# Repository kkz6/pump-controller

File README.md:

# Pump starter controller

Current main-board revision: **DIRECT-R4-PROTOTYPE**. [PCB manufacturing review](verification/dfm-review-2026-11-24/R4/README.md) · [Matching JLC upload bundle](manufacturing/pump-controller-R4-JLC-upload.zip). Supplier placement approval and physical bring-up remain pending.

For the current JLC replacement, use the [local-relay assembly variant](manufacturing/pump-controller-R4-local-relays-JLC-upload.zip): K1/K2 are fitted locally, while J30/J35 remain factory-assembled. The full R4 bundle above remains available for assembling the relays at JLC.

A two-board prototype for an existing 1.5 HP, 220 V single-phase pump starter. The main board measures supply voltage, reads a current transformer and tank probes, and issues starter commands through two PCB-mounted high-inrush changeover relays. The door panel has a plug-in OLED, five operator buttons, an optional key selector and an external button connector. The existing starter switches the motor and capacitors.

| What you need | Files |
| --- | --- |
| Edit the main circuit or board | [Main KiCad project](hardware/main/pump-direct.kicad_pro) · [Schematic PDF](docs/main-schematic.pdf) · [Board drawing](docs/main-board.svg) |
| Edit the door panel | [Panel KiCad project](hardware/panel/pump-panel-rev-f.kicad_pro) · [Schematic PDF](docs/panel-schematic.pdf) · [Panel with display, STEP](mechanical/panel/pump-panel-rev-f-with-display.step) |
| Identify a terminal or relay | [Starter interfaces and connectors](docs/connections.md) |
| Program or recover the processor | [USB bench guide](docs/programming.md) · [Bench firmware](firmware/bench) |
| Request bare boards and assembly | [Manufacturing package and cost](manufacturing/README.md) |
| Order parts and boards | [Order checklist](manufacturing/order-checklist.md) |
| Bring up a new board | [First power-up checks](docs/bring-up.md) |
| Reproduce the design checks | [Verification](verification/README.md) · [Design review 2026-11-21](verification/design-review-2026-11-21.md) |
| See the boards in 3D | [3D views](docs/3d/README.md) · [Main board STL](docs/3d/main.stl) · [Panel STL](docs/3d/panel.stl) |

## Hardware

The main PCB is 100 × 118.5 mm with six copper layers. Relay outputs face outward at the bottom; tank/inlet ports face outward at the top. Printed guides identify K1 with J30 (A) and K2 with J35 (B). R4 uses Omron G5RL-1-E-HR DC5 relays and three-way screw terminals: 1 NO, 2 COM, 3 NC. The full factory-assembly BOM includes the relays and output terminals; the current order uses the local-relay variant linked above. The two outputs can serve a conventional self-holding DOL or a starter with documented remote inputs. Select the control profile for the specific starter. The 60 × 45 mm two-layer panel connects to main J32 through a keyed 12-way cable.

The main board uses an ESP32-C6-MINI-1U-H4 (4 MB flash). The two dedicated programming buttons and USB application indicators are on its low-voltage side. Operator START, STOP, MODE, SET and NEXT are on the panel. The repository includes a flashable USB bench image, control components and tests. Operational wireless firmware, pairing with a particular hub, enclosure fit and physical starter qualification remain open.

The design is at prototype stage. The original DOL STOP and overload must independently interrupt the contactor coil. A welded pickup contact can restart some starters when STOP is released. Review that behavior and the actual coil specification before commissioning. [Interface details](docs/connections.md)

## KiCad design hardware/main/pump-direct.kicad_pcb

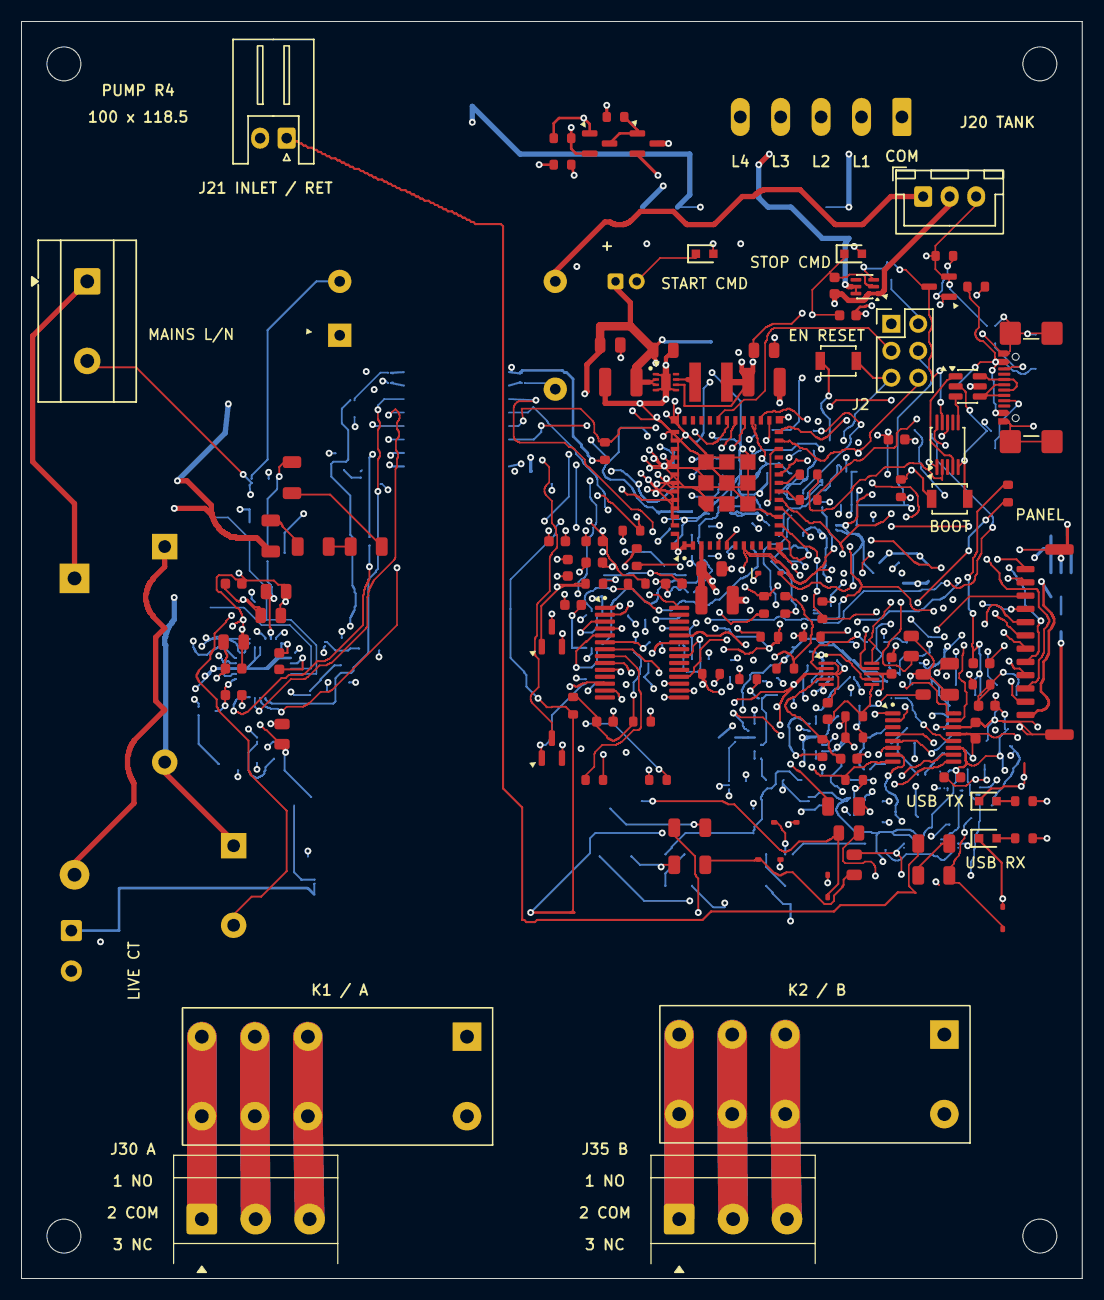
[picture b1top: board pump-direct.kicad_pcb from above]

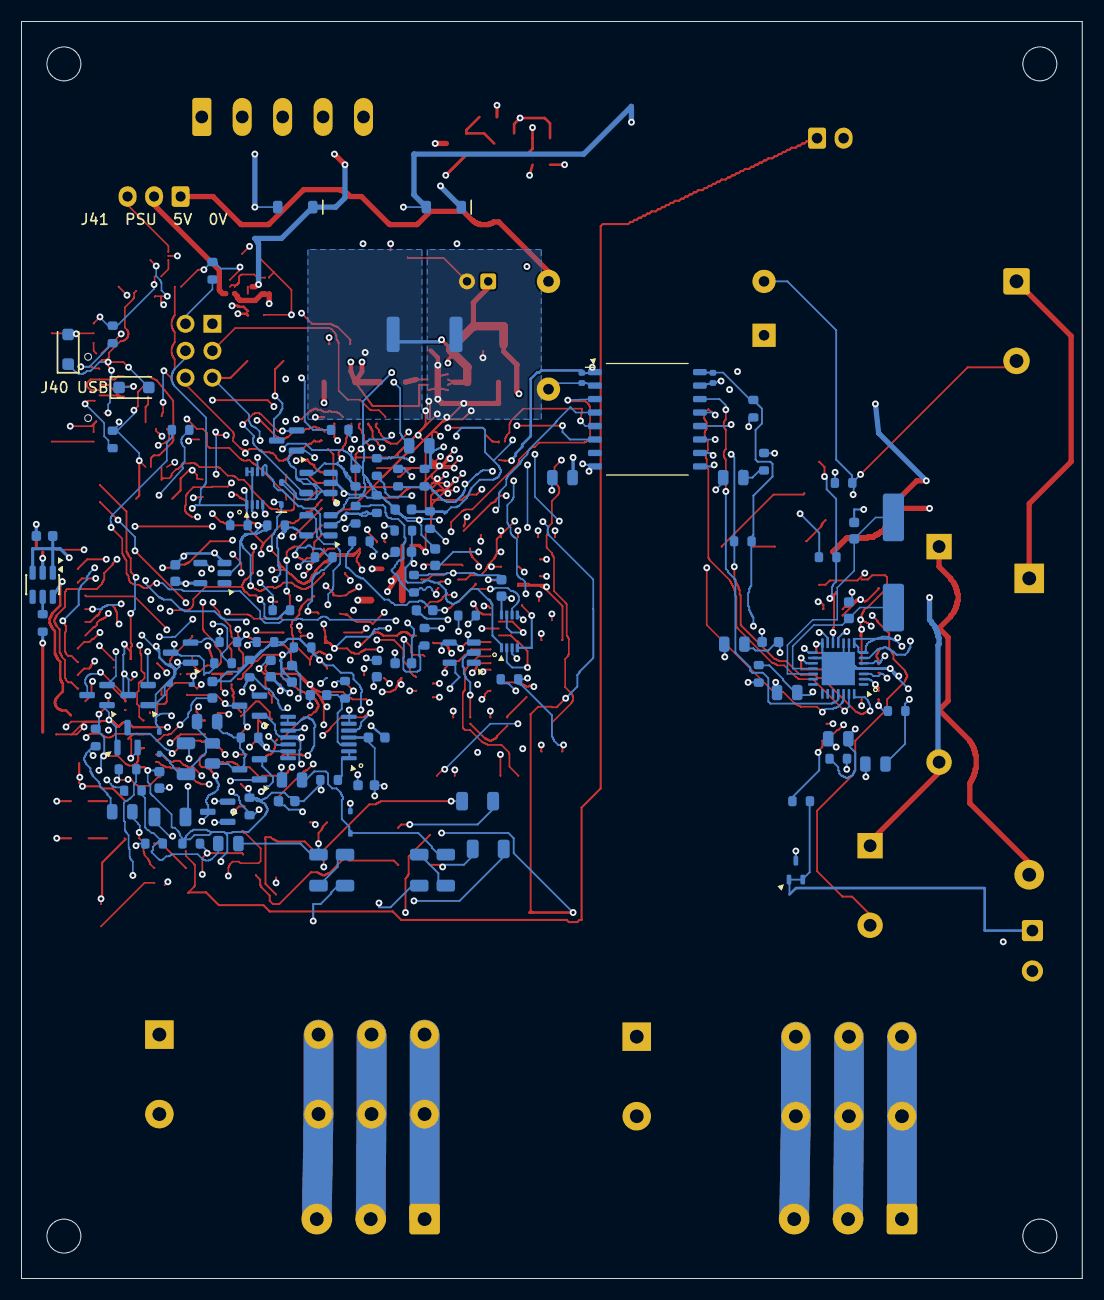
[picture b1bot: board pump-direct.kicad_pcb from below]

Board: 6 copper layers, 100.0 x 118.5 mm, 242 parts (117 on the bottom side), 154 nets.

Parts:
C1: 47uF 25V 105C; CP_Radial_D5_P2_Pads1p5
C2, C4, C6, C21: 1uF 50V X7R; C_0805_2012Metric
C3, C5: 22uF 16V X7R; C_1210_3225Metric
C20: 22uF 10V X7R; C_1210_3225Metric
C22: 1uF 10V X7R; C_0805_2012Metric
C40, C42, C44: 4.7uF; C_0805_2012Metric
C41, C43, C45, C47, C70, C71, C72, C73, C75, C76, C77, C78, C88, C90, C100, C102, C103, C104: 100nF; C_0603_1608Metric
C46, C55, C58: 22uF; C_0805_2012Metric
C48, C74, C101, C105: 1uF; C_0603_1608Metric
C49, C50: 33pF; C_0603_1608Metric
C51, C52, C53, C54: 33nF 50V X7R 10%; C_0805_2012Metric
C57, C60: 100nF; C_0402_1005Metric
C80, C82, C84, C86, C110, C111, C112, C113: 10nF; C_0603_1608Metric
C106, C107, C108, C109, C120, C122, C124, C126, C128: 1uF; C_0805_2012Metric
C121, C123, C125, C127, C129: 1nF; C_0603_1608Metric
C240: 1uF 50V X5R; C_0603_1608Metric
C241, C242, C243: 100nF 16V X7R; C_0603_1608Metric
D10: BAV99W; SOT-323_SC-70
D30, D35: BAT54WS; D_SOD-323
D31, D32: 1N4148W; D_SOD-123
D40: START CMD GREEN; Kingbright_1608_LowCurrent
D41: STOP CMD RED; Kingbright_1608_LowCurrent
D42: USB ESD; SOT-23-6
D43: CLAMP REFERENCE BLOCK; D_SOD-123F
D44: VBUS TVS 6V; D_SOD-123F
D60: USB TX; Kingbright_1608_LowCurrent
D61: USB RX; Kingbright_1608_LowCurrent
D100, D101, D110, D112, D114, D116, D118: PESD5V0S1BA; D_SOD-323
D102, D103, D111, D113, D115, D117, D119: BAS70-04; SOT-23
F1: T1A 600VAC; Fuse_Axial_5x20_P27.94
FB1, FB2: 0R; R_0603_1608Metric
H1, H2, H3, H4: M3 nylon mount; MountingHole_3.2mm_M3
J1: AC INPUT L/N; TerminalBlock_MetzConnect_Type171_RT13702HBWC_1x02_P7.50mm_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
J2: SERVICE 2x3; PinHeader_2x03_P2.54mm_Vertical
J10: LIVE CT / FIXED; TerminalBlock_Phoenix_MKDS-1-2-3.81_1x02_P3.81mm_Horizontal
J20: TANK PROBES; PhoenixContact_MC_1,5_5-G-3.81_1x05_P3.81mm_Horizontal
J21: INLET / RETURN; JST_XH_S2B-XH-A_1x02_P2.50mm_Horizontal
J30: OUT A / NO-COM-NC; MKDS3_3_508_Power
J32: PANEL / GH12; JST_GH_SM12B-GHS-TB_1x12-1MP_P1.25mm_Horizontal
J35: OUT B / NO-COM-NC; MKDS3_3_508_Power
J40: USB-C DATA / SERVICE; USB_C_GCT_USB4110_12Lands
J41: RUN LINK / BENCH 5V; JST_XH_B3B-XH-A_1x03_P2.50mm_Vertical
K1, K2: G5RL-1-E-HR DC5; G5RL_1_E_HR
L1: 2.2uH; L_Sunlord_SWPA4030S
Q30, Q31: AO3400A; SOT-23
Q40: VBUS INHIBIT; SOT-23
Q50: STOP COIL HIGH SIDE; SOT-23
Q51: STOP PERMIT INVERTER; SOT-23
R1: 22R 3W FUSIBLE; R_Axial_L13_D6_P20.32
R2: 33R 1% 2W MINIMUM LOAD; R_2512_6332Metric_DNP_NoPaste
R20, R21, R22, R26, R40, R41, R80, R82, R84, R89, R91, R100, R101, R109: 10k; R_0603_1608Metric
R24, R25, R71, R72, R77, R78, R115, R118: 2.2k; R_0603_1608Metric
R27, R28, R76: 22R; R_0603_1608Metric
R42: 0R; R_0603_1608Metric
R43, R44, R45, R46: 249k; R_1206_3216Metric
R47, R48, R49, R50, R88, R90, R110, R112, R190, R191, R260, R261: 1k; R_0603_1608Metric
R70, R132, R142, R152, R162, R172: 47k; R_0603_1608Metric
R74: 100R; R_0603_1608Metric
R75, R87, R92, R93, R105, R106, R107, R108: 100k; R_0603_1608Metric
R81, R83, R85, R104: 33k; R_0603_1608Metric
R86, R103, R133, R143, R153, R163, R173: 22k; R_0603_1608Metric
R102, R111, R113: 100; R_0603_1608Metric
R114: 1M; R_0603_1608Metric
R116, R117, R119, R120, R130, R131, R140, R141, R150, R151, R160, R161, R170, R171: 10k; R_1206_3216Metric
R240, R241: 5.1k 1%; R_0603_1608Metric
R242: 1k 1%; R_0603_1608Metric
R243: 47k 1%; R_0603_1608Metric
R244, R247: 10k 1%; R_0603_1608Metric
R245: 210k 1%; R_0603_1608Metric
R246, R248: 100k 1%; R_0603_1608Metric
RV1: TMOV 320VAC; TMOV14_Inline_P7.5
SW60: BOOT; SW_SPST_B3U-1000P
SW61: EN RESET; SW_SPST_B3U-1000P
U1: 5V 1.2A ISOLATED; RACM06E
U2: TPS62162 3V3 1A; Texas_DSG0008A_WSON-8-1EP_2x2mm_P0.5mm_EP0.9x1.6mm
U3: ESP32-C6-MINI-1U-H4; ESP32-C6-MINI-1U
U10: ADE7953ACPZ; LFCSP-28-1EP_5x5mm_P0.5mm_EP3.14x3.14mm
U11: CA-IS3641HW; CA-IS3641_SOIC16W_Dense
U20: TLV9004; TSSOP-14_4.4x5mm_P0.65mm
U21: TMUX1208; TSSOP-16_4.4x5mm_P0.65mm
U22: ADS1115; TSSOP-10_3x3mm_P0.5mm
U30: STWD100NYWY3F / 1.6s; SOT-23-5
U31: SN74LVC1G74DCUR; SN74LVC1G74_DCU_TI
U32: MCP120T-300I/TT; SOT-23
U33: MCP23017-E/SS; SSOP-28_5.3x10.2mm_P0.65mm
U34: 74LVC1G08GV; SOT-23-5
U35, U36: SN74LVC1G17DBVR; SOT-23-5
U37: 74LVC3G17DC; SN74LVC3G17_DCU_TI
U40: USB MOTOR INHIBIT; SOT-363_SC-70-6
U41: USB DATA SWITCH; MSOP-10_3x3mm_P0.5mm
U42: PANEL 5V LIMIT; SOT-23-6
Y1: 3.579545MHz / CL20pF; Crystal_SMD_HC49-SD

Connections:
+3V3: C5.1, C6.1, C20.1, C21.1, C57.1, C70.1, C71.1, C72.1, C73.1, C74.1, C75.1, C76.1, C77.1, C78.1, C102.1, C103.1, C104.1, C105.1, C241.1, D102.2, D103.2, D111.2, D113.2, D115.2, D117.2, D119.2, J2.2 (3V3_SENSE), J32.8 (+3V3), L1.2, R20.1, R21.1, R22.1, R24.1, R25.1, R26.1, R70.1, R89.1, R91.1, R100.1, R109.2, R244.1, U2.6, U3.3, U11.1, U20.4, U21.2, U21.13, U22.8, U30.5, U31.2, U31.7, U31.8, U32.2, U33.9 (VDD), U34.5, U35.5, U36.5, U37.8, U41.10 (VCC)
+5V: C1.1, C2.1, C3.1, C4.1, C55.1, C240.1, J41.2 (BOARD_5V), R2.1, U2.2, U2.3, U40.1 (VIN)
+5V_CMD: C242.1, C243.1, D32.1 (K), K2.8, Q50.2, R246.1, U40.5 (QOD), U40.6 (VOUT), U42.1, U42.3
ARM_CLEAR_N: U31.6, U36.4
ARM_CMD: J2.4 (ARM_TEST), R78.1, U3.30, U31.1
ARM_Q: U31.5, U34.1
AUTO_RETURN: J32.4 (AUTO_RETURN), R84.1
AUTO_SENSE: U33.5 (GPB4), U37.2
AUTO_SENSE_RAW: C84.1, R84.2, R85.1, U37.6
BOOT: J2.6 (BOOT_N), R21.2, SW60.1, U3.23
BUCK_SW: L1.1, U2.7
CMD_ALLOWED: Q40.3, R244.2, U40.3 (ON), U41.9 (OE_N)
CTRL_A_COM: J30.2, K1.3, K1.6
CTRL_A_NC: J30.3, K1.2, K1.7
CTRL_A_NO: J30.1, K1.4, K1.5
CTRL_B_COM: J35.2, K2.3, K2.6
CTRL_B_NC: J35.3, K2.2, K2.7
CTRL_B_NO: J35.1, K2.4, K2.5
GND: C1.2, C2.2, C3.2, C4.2, C5.2, C6.2, C20.2, C21.2, C22.2, C55.2, C57.2, C70.2, C71.2, C72.2, C73.2, C74.2, C75.2, C76.2, C77.2, C78.2, C80.2, C82.2, C84.2, C86.2, C88.2, C90.2, C100.2, C101.2, C102.2, C103.2, C104.2, C105.2, C110.2, C111.2, C112.2, C113.2, C240.2, C241.2, C242.2, C243.2, D40.1 (K), D41.1 (K), D42.2 (GND), D44.2 (A), D60.1 (K), D61.1 (K), D100.2, D101.2, D102.1, D103.1, D110.2, D111.1, D112.2, D113.1, D114.2, D115.1, D116.2, D117.1, D118.2, D119.1, J2.1 (GND), J32.7 (GND), J32.MP (MOUNT), J40.A1 (GND_A1_B12), J40.A12 (GND_A12_B1), J40.SH (SHIELD), J41.3 (RETURN), Q30.2, Q31.2, Q40.2, Q51.2, R2.2, R71.2, R72.2, R75.2, R77.2, R78.2, R81.2, R83.2, R85.2, R87.2, R92.2, R93.2, R101.2, R105.2, R106.2, R107.2, R108.2, R240.2, R241.2, R243.2, R245.2, R248.2, SW60.2, SW61.2, U1.4 (-VOUT), U2.1, U2.4, U2.5, U2.9, U3.1, U3.2, U3.11, U3.14, U3.36, U3.37, U3.38, U3.39, U3.40, U3.41, U3.42, U3.43, U3.44, U3.45, U3.46, U3.47, U3.48, U3.49, U3.50, U3.51, U3.52, U3.53, U11.2, U11.8, U20.11, U21.14, U22.1, U22.3, U30.2, U30.3, U31.4, U32.3, U33.10 (VSS), U33.15 (A0), U33.16 (A1), U33.17 (A2), U34.3, U35.3, U36.3, U37.4, U40.2 (GND), U41.1 (SEL), U41.5 (GND), U42.2
HEARTBEAT: R71.1, U3.27, U30.4
HH_SENSE: C86.1, R86.2, R87.1, U35.2
I2C_SCL: J32.10 (I2C_SCL), R25.2, U3.29, U22.10, U33.12 (SCL)
I2C_SDA: J32.9 (I2C_SDA), R24.2, U3.28, U22.9, U33.13 (SDA)
INTERLOCK_OK: D35.1, U33.6 (GPB5), U35.4
K1_5V: D31.1 (K), K1.8, Q50.3
K1_GATE: Q30.1, R74.2, R75.1
K1_LOW: D31.2 (A), K1.1, Q30.3
K1_PBASE: Q51.1, R247.2, R248.1
K1_PGATE: Q50.1, Q51.3, R246.2
K2_GATE: Q31.1, R76.2, R77.1
K2_LOW: D32.2 (A), K2.1, Q31.3
L_FUSED: F1.2, R1.1
L_PROTECTED: R1.2, R43.1, RV1.1, U1.1 (AC_L)
MAINS_L: F1.1, J1.1 (L)
MAINS_N: J1.2 (N), R42.1, RV1.2, U1.2 (AC_N)
MAN_RETURN: J32.3 (MAN_RETURN), R82.1
MAN_SENSE: U33.4 (GPB3), U37.5
MAN_SENSE_RAW: C82.1, R82.2, R83.1, U37.3
MCU_EN: C22.1, D30.1, J2.5 (RESET_N), R20.2, SW61.1, U3.8, U33.18 (RESET_N)
METER_CS: R26.2, U3.24, U11.5
METER_MISO: U3.19, U11.6
METER_MOSI: U3.16, U11.4
METER_SCLK: U3.15, U11.3
MUX_A0: R106.1, U3.13, U21.1
MUX_A1: R107.1, U3.5, U21.16
MUX_A2: R108.1, U3.6, U21.15
M_3V3: C46.1, C47.1, C60.1, FB1.2, R40.1, R41.1, U10.7, U10.8, U10.17, U11.16
M_CS: R41.2, U10.28, U11.12
M_CT_HI: D10.1, D10.2, J10.1, R49.1
M_GND: C40.2, C41.2, C42.2, C43.2, C44.2, C45.2, C46.2, C47.2, C48.2, C49.2, C50.2, C51.2, C52.2, C53.2, C54.2, C60.2, D10.3, FB2.2, J10.2, R42.2, R47.2, R48.1, R50.1, U10.4, U10.9, U10.10, U10.14, U10.16, U10.29, U11.9, U11.10, U11.15
M_IAN: C54.1, R50.2, U10.6
M_IAP: C53.1, R49.2, U10.5
M_ISO_GND: C58.2, FB2.1
M_ISO_RAW: C58.1, FB1.1
M_MISO: U10.26, U11.11
M_MOSI: U10.27, U11.13
M_REF: C44.1, C45.1, U10.13
M_RESET_N: C48.1, R40.2, U10.2
M_SCLK: U10.25, U11.14
M_VDIV_0: R43.2, R44.1
M_VDIV_1: R44.2, R45.1
M_VDIV_2: R45.2, R46.1
M_VINTA: C42.1, C43.1, U10.15
M_VINTD: C40.1, C41.1, U10.3
M_VN: C52.1, R48.2, U10.11
M_VP: C51.1, R46.2, R47.1, U10.12
M_XIN: C49.1, U10.18, Y1.1
M_XOUT: C50.1, U10.19, Y1.2
PANEL_5V: J32.1 (+5V), U42.6
PANEL_ILIM: R245.1, U42.5
PERMIT_D: R72.1, U3.26, U34.2
PERMIT_Q: R74.1, U34.4
PROBE_ADC_BIAS: C111.1, R111.2, U22.5
PROBE_ADC_BIAS2: C113.1, R113.2, U22.7
PROBE_ADC_RDY: R109.1, U22.2
PROBE_ADC_SIGNAL: C110.1, R110.2, U22.4
PROBE_ADC_TX: C112.1, R112.2, U22.6
PROBE_BIAS: C101.1, C121.2, C123.2, C125.2, C127.2, C129.2, R102.2, R104.1, R111.1, R113.1, R114.2, R132.2, R142.2, R152.2, R162.2, R172.2, U21.11
PROBE_BIAS_DIV: C100.1, R100.2, R101.1, U20.3
PROBE_BIAS_RAW: R102.1, U20.1, U20.2
PROBE_EXC: R103.1, R105.1, U3.12
PROBE_ICOM: J21.2, R120.2
PROBE_ICOM_CLAMP: C107.2, C109.2, D101.1, R119.1
PROBE_ICOM_DRIVE: C107.1, C109.1, D103.3, R118.2
PROBE_ICOM_MID: R119.2, R120.1
PROBE_INLET: J21.1, R170.1
PROBE_INLET_ADC: C129.1, D119.3, R173.2, U21.12
PROBE_INLET_CLAMP: C128.1, D118.1, R171.2
PROBE_INLET_MID: R170.2, R171.1
PROBE_INLET_SENSE: C128.2, R172.1, R173.1
PROBE_L1: J20.2, R130.1
PROBE_L1_ADC: C121.1, D111.3, R133.2, U21.4
PROBE_L1_CLAMP: C120.1, D110.1, R131.2
PROBE_L1_MID: R130.2, R131.1
PROBE_L1_SENSE: C120.2, R132.1, R133.1
PROBE_L2: J20.3, R140.1
PROBE_L2_ADC: C123.1, D113.3, R143.2, U21.5
PROBE_L2_CLAMP: C122.1, D112.1, R141.2
PROBE_L2_MID: R140.2, R141.1
PROBE_L2_SENSE: C122.2, R142.1, R143.1
PROBE_L3: J20.4, R150.1
PROBE_L3_ADC: C125.1, D115.3, R153.2, U21.6
PROBE_L3_CLAMP: C124.1, D114.1, R151.2
PROBE_L3_MID: R150.2, R151.1
PROBE_L3_SENSE: C124.2, R152.1, R153.1
PROBE_L4: J20.5, R160.1
PROBE_L4_ADC: C127.1, D117.3, R163.2, U21.7
PROBE_L4_CLAMP: C126.1, D116.1, R161.2
PROBE_L4_MID: R160.2, R161.1
PROBE_L4_SENSE: C126.2, R162.1, R163.1
PROBE_MUX_BUF: R110.1, U20.8, U20.9
PROBE_MUX_OUT: R114.1, U20.10, U21.8
PROBE_TCOM: J20.1, R117.2
PROBE_TCOM_CLAMP: C106.2, C108.2, D100.1, R116.1
PROBE_TCOM_DRIVE: C106.1, C108.1, D102.3, R115.2
PROBE_TCOM_MID: R116.2, R117.1
PROBE_TX_INLET: R118.1, U20.13, U20.14, U21.9
PROBE_TX_SET: R103.2, R104.2, U20.5, U20.12
PROBE_TX_TANK: R112.1, R115.1, U20.6, U20.7, U21.10
PSU_5V_RAW: J41.1 (PSU), U1.5 (+VOUT)
RESET_FILTER: C90.1, R90.2, R91.2, U33.2 (GPB1)
RESET_N: J32.6 (RESET_N), R90.1
RUN_CMD: R76.1, U3.25
SAFE_CLEAR_N: D30.2, D35.2, R70.2, U30.1, U32.1, U36.2
SPARE_B6: J32.11 (SPARE_B6), R92.1, U33.7 (GPB6)
SPARE_B7: J32.12 (SPARE_B7), R93.1, U33.21 (GPA0)
START_CMD_LED: R190.1, U33.8 (GPB7)
START_FILTER: C88.1, R88.2, R89.2, U33.1 (GPB0)
START_LED_A: D40.2 (A), R190.2
START_N: J32.5 (START_N), R88.1
STOP_CMD_LED: R191.1, U33.28 (GPA7)
STOP_LED_A: D41.2 (A), R191.2
STOP_RETURN: J32.2 (STOP_RETURN), R80.1, R86.1, R247.1
STOP_SENSE: U33.3 (GPB2), U37.7
STOP_SENSE_RAW: C80.1, R80.2, R81.1, U37.1
STRAP_GPIO8: R22.2, U3.22
UART_TX: J2.3 (TXD0), U3.31
USB_CC1: J40.A5 (CC1), R240.1
USB_CC2: J40.B5 (CC2), R241.1
USB_CONN_DM: D42.4 (IO2), J40.A7 (D-), J40.B7 (D-)
USB_CONN_DP: D42.6 (IO1), J40.A6 (D+), J40.B6 (D+)
USB_DM: R27.2, U41.8 (D1-)
USB_DM_MCU: R27.1, U3.17
USB_DP: R28.2, U41.2 (D1+)
USB_DP_MCU: R28.1, U3.18
USB_ESD_REF: D42.5 (VBUS), D43.1 (K)
USB_PRESENT: Q40.1, R242.2, R243.1
USB_PROT_DM: D42.3 (IO2), U41.6 (D-)
USB_PROT_DP: D42.1 (IO1), U41.4 (D+)
USB_RX_IND: R261.1, U33.24
USB_RX_LED_A: D61.2 (A), R261.2
USB_TX_IND: R260.1, U33.23 (GPA2)
USB_TX_LED_A: D60.2 (A), R260.2
USB_VBUS: D43.2 (A), D44.1 (K), J40.A4 (VBUS_A4_B9), J40.A9 (VBUS_A9_B4), R242.1

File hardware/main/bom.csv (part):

Reference,Value,MPN,Description,Footprint,Datasheet,Sheet,DNP
J1,AC INPUT L/N,KF128-7.5-2P,"Cixi Kefa KF128-7.5, 2 positions on 7.50 mm pitch, rising-clamp screw terminal; UL 300 V 10 A, IEC 450 V 24 A OVC III. Pin 1 line, pin 2 neutral. Body is 0.5 mm wider than the Metz Type 171 courtyard; the footprint's 1.3 mm holes take its 0.8 mm pins.",CompactGuard:TerminalBlock_MetzConnect_Type171_RT13702HBWC_1x02_P7.50mm_Horizontal,https://jlcpcb.com/parts/componentSearch?searchTxt=C474954,power,False
F1,T1A 600VAC,0ADKP1000-RE,Bel 1 A time-delay axial pigtail fuse; 200 A interrupting capacity at 600 VAC; coordinate with upstream protection,Pump:Fuse_Axial_5x20_P27.94,https://www.belfuse.com/media/datasheets/products/circuit-pr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,power,False
R1,22R 3W FUSIBLE,AC03000002209JACCS,Vishay AC03-CS 22 ohm 3 W 5% fusible safety resistor; keep heat away from MCU and capacitors,Pump:R_Axial_L13_D6_P20.32,https://www.vishay.com/docs/28909/acxxcs.pdf,power,False
RV1,TMOV 320VAC,TMOV14RP320EL2T7,"Thermally protected 14 mm MOV, 320 VAC continuous; INLINE crimped L2 lead option (L2T7 tape or L2B7 bulk) required for footprint; surge coordination unverified",Pump:TMOV14_Inline_P7.5,https://www.littelfuse.com/assetdocs/tmov-itmov?assetguid=bd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,power,False
U1,5V 1.2A ISOLATED,RACM06E-05SK/277,"6 W reinforced-isolation AC/DC module, 25.4 x 25.4 x 16.7 mm; 5 V model delivers 6 W to 50 C at 115-277 VAC; keep output floating",Pump:RACM06E,https://recom-power.com/pdf/Powerline_AC-DC/RACM06E-K_277.pdf,power,False
C1,47uF 25V 105C,NXB25V47M5*11 LO,"SamYoung NXB, 47 uF, 25 V, 105 C, D5 x 11 mm. Front mounted on 2 mm lead pitch. Allow a 5.5 mm maximum diameter and 12.5 mm maximum length, up to 1 mm seating gap and up to 3 mm lead projection on the rear.",PumpRevE:CP_Radial_D5_P2_Pads1p5,https://jlcpcb.com/partdetail/SamYoungElectronics-NXB25V47M5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,power,False
C2,1uF 50V X7R,Generic 1uF 50V X7R 0805,Local ceramic bypass; X7R dielectric; verify effective capacitance at bias,Capacitor_SMD:C_0805_2012Metric,,power,False
C3,22uF 16V X7R,CL32B226KOJNNNE,"Samsung CL32B 1210, 22 uF, 16 V X7R, 10%. Buck VIN bypass. Verify at least 10 uF effective at operating bias and temperature.",Capacitor_SMD:C_1210_3225Metric,https://jlcpcb.com/partdetail/56557-CL32B226KOJNNNE/C55530,power,False
C4,1uF 50V X7R,Generic 1uF 50V X7R 0805,Buck high-frequency input bypass directly at VIN/PGND,Capacitor_SMD:C_0805_2012Metric,,power,False
U2,TPS62162 3V3 1A,TPS62162DSGR,"Fixed3.3V buck; FB to AGND, VOS Kelvin to output capacitor. Solder EP to GND; two external0.65/0.30mm GND vias, no holes in SMT land.",Package_SON:Texas_DSG0008A_WSON-8-1EP_2x2mm_P0.5mm_EP0.9x1.6mm,https://www.ti.com/lit/ds/symlink/tps62160.pdf,power,False
L1,2.2uH,SWPA4030S2R2MT,"Sunlord SWPA4030S, 4.0x4.0x3.0 mm; manufacturer land pattern: two 1.10x3.70 mm pads at +/-1.50 mm, 1.90 mm gap. Non-polarized. 2.2 uH 20%, 4.9 A saturation, 39 mOhm max DCR.",Inductor_SMD:L_Sunlord_SWPA4030S,https://jlcpcb.com/partdetail/Sunlord-SWPA4030S2R2MT/C36409,power,False
C5,22uF 16V X7R,CL32B226KOJNNNE,"Samsung CL32B 1210, 22 uF, 16 V X7R, 10%. Buck output bypass at the VOS sense point. Verify filter stability and rail load steps.",Capacitor_SMD:C_1210_3225Metric,https://jlcpcb.com/partdetail/56557-CL32B226KOJNNNE/C55530,power,False
C6,1uF 50V X7R,Generic 1uF 50V X7R 0805,Local 3.3 V rail bypass,Capacitor_SMD:C_0805_2012Metric,,power,False
R2,33R 1% 2W MINIMUM LOAD,CRM2512-FX-33R0ELF,"DNP: RECOM RACM06E minimum load is 0%, so no preload is fitted; footprint kept. Was Bourns 2512 thick-film 33 ohm 1%, 2 W at 70 C with 300 mm2 combined solder-pad/trace copper per datasheet; permanent 5 V minimum-load resistor, 0.677-0.844 W at 4.75-5.25 V including 1% tolerance. Reserve copper area and keep away from probes, precision meter components, antenna module and electrolytics. Revised module local ambient limit 50 C.",PumpRevE:R_2512_6332Metric_DNP_NoPaste,https://www.bourns.com/docs/product-datasheets/crm.pdf,power,True
U3,ESP32-C6-MINI-1U-H4,ESP32-C6-MINI-1U-H4,4 MB flash (H8 out of stock at JLC; same module and footprint); external antenna; hardware supports Matter over Wi-Fi or Thread. Antenna must be outside metal starter enclosure. GPIO17 drives ARM_CMD interlock rearm; GPIO16 UART TX logs only; GPIO4/5/15 unused; strap levels preserved.,Pump:ESP32-C6-MINI-1U,https://documentation.espressif.com/esp32-c6-mini-1_mini-1u_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,mcu,False
C20,22uF 10V X7R,Generic 22uF 10V X7R 1210,Module bulk capacitor adjacent to pin 3; effective capacitance >=10 uF at 3.3 V,Capacitor_SMD:C_1210_3225Metric,,mcu,False
C21,1uF 50V X7R,Generic 1uF 50V X7R 0805,Module bypass immediately at pin 3 and ground pads,Capacitor_SMD:C_0805_2012Metric,,mcu,False
C22,1uF 10V X7R,Generic 1uF 10V X7R 0805,Enable RC delay with R20; watchdog/supervisor uses open-drain reset only,Capacitor_SMD:C_0805_2012Metric,,mcu,False
R20,10k,"SPEC: 10k 1%, 0.1W, 0603",Module EN pull-up; 10 ms nominal RC with C22,Resistor_SMD:R_0603_1608Metric,,mcu,False
R21,10k,"SPEC: 10k 1%, 0.1W, 0603",GPIO9 boot strap pull-up. An isolated programmer may pull J2.6 low during reset through J2.5 for USB download.,Resistor_SMD:R_0603_1608Metric,,mcu,False
R22,10k,"SPEC: 10k 1%, 0.1W, 0603",GPIO8 must be high while GPIO9 is low to enter serial download mode,Resistor_SMD:R_0603_1608Metric,,mcu,False
R24,2.2k,"SPEC: 2.2k 1%, 0.1W, 0603",I2C SDA pull-up; populate one pull-up set on assembled controller,Resistor_SMD:R_0603_1608Metric,,mcu,False
R25,2.2k,"SPEC: 2.2k 1%, 0.1W, 0603",I2C SCL pull-up; verify bus capacitance/rise time at selected clock,Resistor_SMD:R_0603_1608Metric,,mcu,False
R26,10k,"SPEC: 10k 1%, 0.1W, 0603",Keep metering IC deselected while ESP32 is resetting,Resistor_SMD:R_0603_1608Metric,,mcu,False
R27,22R,"SPEC: 22R 1%, 0.1W, 0603",Optional internal USB service path; series resistor adjacent to module,Resistor_SMD:R_0603_1608Metric,,mcu,False
R28,22R,"SPEC: 22R 1%, 0.1W, 0603",Optional internal USB service path; route D+/D- as 90-ohm differential pair,Resistor_SMD:R_0603_1608Metric,,mcu,False
J2,SERVICE 2x3,Samtec TSW-103-07-G-D,SELV fixture for BOOT / EN / logic debug. Pin 2 is a 3.3 V sense only. Board power at J41. Native USB is at J40.,CompactGuard:PinHeader_2x03_P2.54mm_Vertical,,mcu,False
U10,ADE7953ACPZ,ADE7953ACPZ,Single phase metering IC; poll registers through SPI at 1MHz,Package_CSP:LFCSP-28-1EP_5x5mm_P0.5mm_EP3.14x3.14mm,https://www.analog.com/media/en/technical-documentation/data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,meter_ic,False
C40,4.7uF,"SPEC: 4.7uF X5R or X7R, 10%, >=16V","X5R or X7R, 10%, >=16V",Capacitor_SMD:C_0805_2012Metric,,meter_ic,False
C41,100nF,"SPEC: 100nF X7R, 10%, 16V","X7R, 10%, 16V",Capacitor_SMD:C_0603_1608Metric,,meter_ic,False
C42,4.7uF,"SPEC: 4.7uF X5R or X7R, 10%, >=16V","X5R or X7R, 10%, >=16V",Capacitor_SMD:C_0805_2012Metric,,meter_ic,False
C43,100nF,"SPEC: 100nF X7R, 10%, 16V","X7R, 10%, 16V",Capacitor_SMD:C_0603_1608Metric,,meter_ic,False
C44,4.7uF,"SPEC: 4.7uF X5R or X7R, 10%, >=16V","X5R or X7R, 10%, >=16V",Capacitor_SMD:C_0805_2012Metric,,meter_ic,False
C45,100nF,"SPEC: 100nF X7R, 10%, 16V","X7R, 10%, 16V",Capacitor_SMD:C_0603_1608Metric,,meter_ic,False
C46,22uF,"SPEC: 22uF X5R or X7R, 20%, >=10V","X5R or X7R, 20%, >=10V, 0805",Capacitor_SMD:C_0805_2012Metric,,meter_ic,False
C47,100nF,"SPEC: 100nF X7R, 10%, 16V","X7R, 10%, 16V",Capacitor_SMD:C_0603_1608Metric,,meter_ic,False
R40,10k,"SPEC: 10k 1%, 0.1W, 0603","1%, 0.1W, 0603",Resistor_SMD:R_0603_1608Metric,,meter_ic,False
C48,1uF,"SPEC: 1uF X5R or X7R, 10%, >=16V","X5R or X7R, 10%, >=16V",Capacitor_SMD:C_0603_1608Metric,,meter_ic,False
R41,10k,"SPEC: 10k 1%, 0.1W, 0603","1%, 0.1W, 0603",Resistor_SMD:R_0603_1608Metric,,meter_ic,False
Y1,3.579545MHz / CL20pF,X49SM3579545MSD2SC-1,"YXC HC-49S SMD, 20 pF load, 20 ppm. 33 pF caps with about 4.5 pF stray give about 21 pF; confirm start-up and accuracy at bring-up.",Crystal:Crystal_SMD_HC49-SD,https://jlcpcb.com/partdetail/2606-X49SM3579545MSD2SC1/C2237,meter_ic,False
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
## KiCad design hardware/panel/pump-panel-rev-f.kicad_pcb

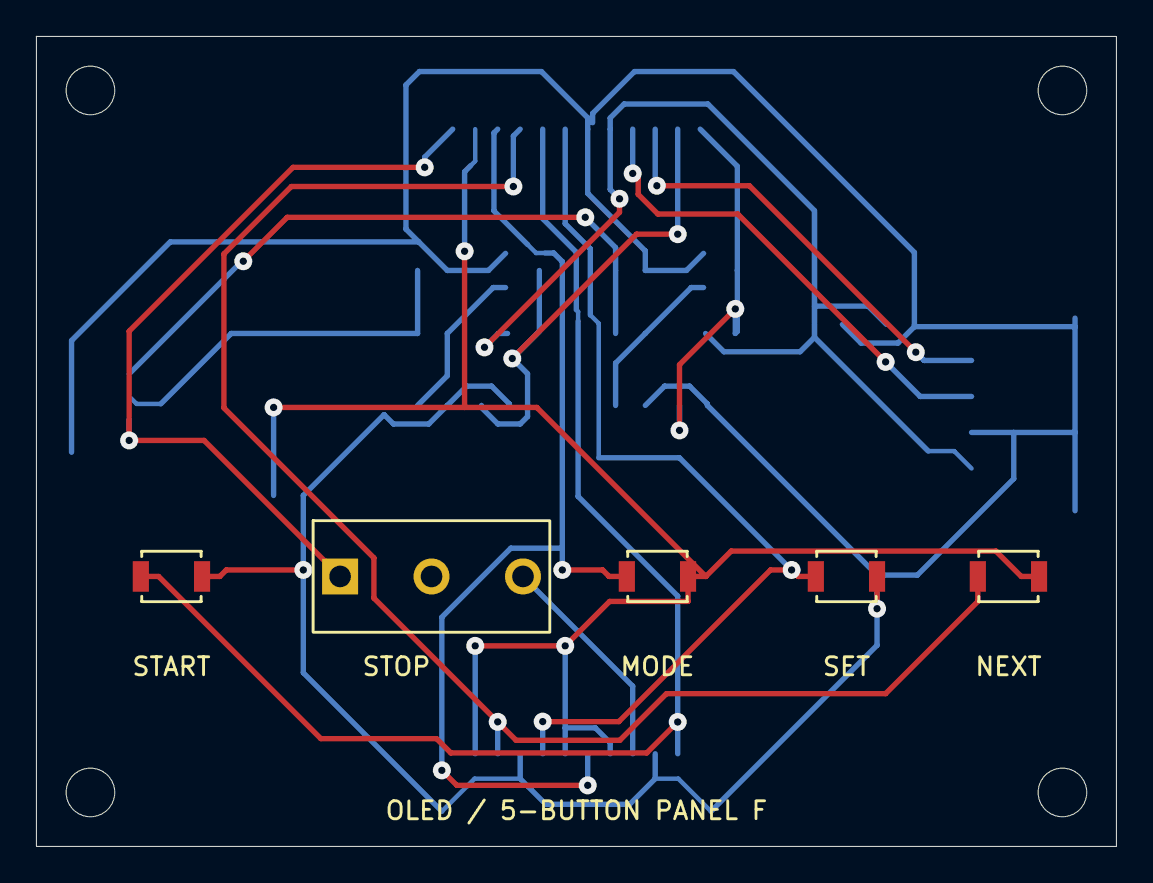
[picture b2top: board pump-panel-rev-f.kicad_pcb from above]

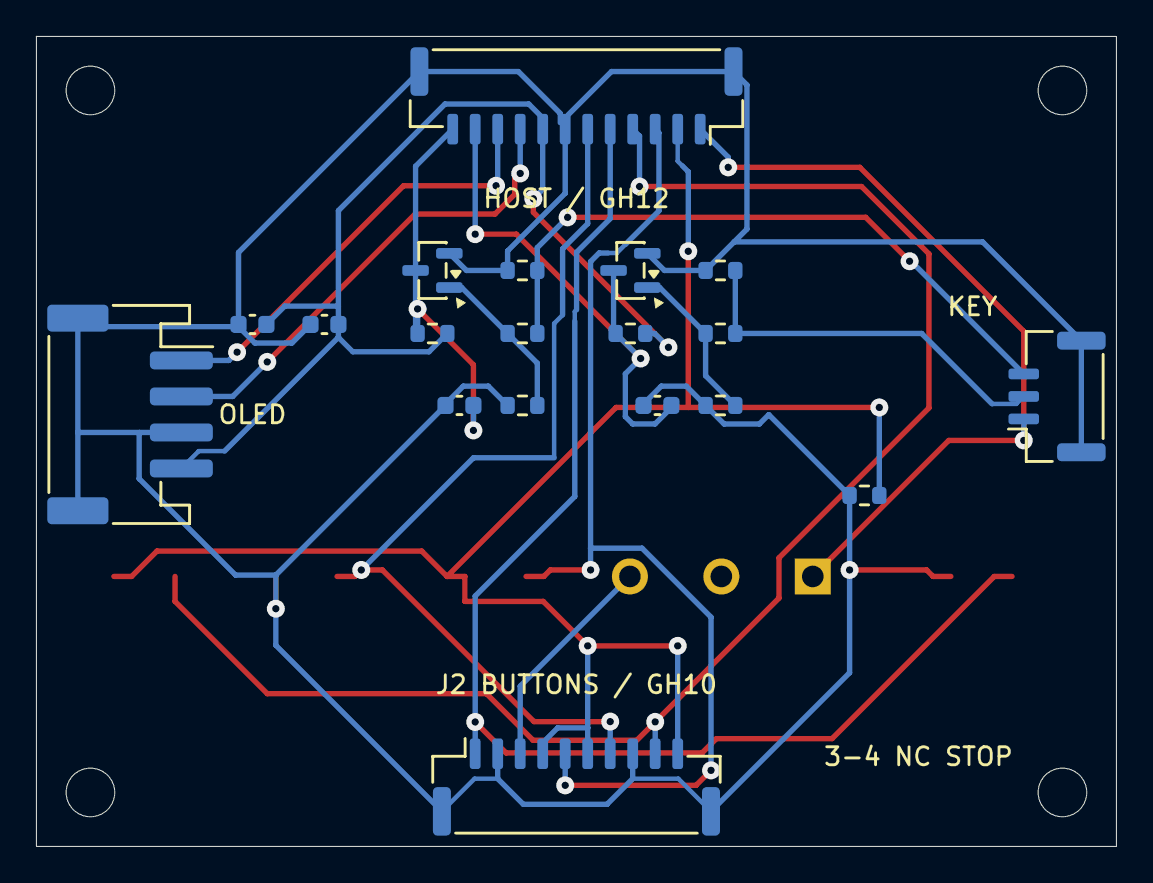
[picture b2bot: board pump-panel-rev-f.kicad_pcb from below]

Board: 2 copper layers, 60.0 x 45.0 mm, 28 parts (19 on the bottom side), 17 nets.

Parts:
C1: 100nF; C_0603_1608Metric
C2: 4.7uF; C_0603_1608Metric
C3, C4: 10nF; C_0603_1608Metric
H1, H2, H3, H4: M2.5 mount; MountingHole_2.7mm_M2.5
J1: MAIN / JST GH 12; JST_GH_SM12B-GHS-TB_1x12-1MP_P1.25mm_Horizontal
J2: REMOTE BUTTON STATION / GH10; JST_GH_SM10B-GHS-TB_1x10-1MP_P1.25mm_Horizontal
J7: OLED / PH4; JST_PH_S4B-PH-SM4-TB_1x04-1MP_P2.00mm_Horizontal
J8: KEY / JST GH 3; JST_GH_SM03B-GHS-TB_1x03-1MP_P1.25mm_Horizontal
Q1, Q2: MMBT3904; SOT-23
R1, R2, R6: 2.2k; R_0603_1608Metric
R3, R5, R7, R9: 10k; R_0603_1608Metric
R4, R8: 100k; R_0603_1608Metric
SW1: STOP / NC; Omron_D2F-01F
SW2: START; SW_SPST_B3U-1000P
SW3: AUTO / MANUAL; SW_SPST_B3U-1000P
SW4: SET / RESET; SW_SPST_B3U-1000P
SW5: NEXT / +; SW_SPST_B3U-1000P

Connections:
+3V3: C1.1, C2.1, J1.8, J7.4, R5.1, R9.1
+5V: J1.1, J8.1, SW1.1
AUTO_RETURN: J1.4, J2.9, SW5.1
GND: C1.2, C2.2, C3.2, C4.2, J1.7, J1.MP, J2.2, J2.8, J2.MP, J7.3, J7.MP, J8.MP, Q1.2, Q2.2, R1.2, R2.2, R4.2, R6.2, R8.2, SW2.2, SW4.2
I2C_SCL: J1.10, J7.1
I2C_SDA: J1.9, J7.2
KEY_AUTO_B: Q2.1, R7.2, R8.1
KEY_AUTO_N: C4.1, J1.12, Q2.3, R9.2
KEY_AUTO_RAW: J8.3, R6.1, R7.1
KEY_MAN_B: Q1.1, R3.2, R4.1
KEY_MAN_N: C3.1, J1.11, Q1.3, R5.2
KEY_MAN_RAW: J8.2, R2.1, R3.1
MAN_RETURN: J1.3, J2.5, SW3.1
RESET_N: J1.6, J2.7, SW4.1
START_N: J1.5, J2.1, SW2.1
STOP_LOCAL_NC: J2.3, SW1.3
STOP_RETURN: J1.2, J2.4, J2.6, J2.10, R1.1, SW3.2, SW5.2

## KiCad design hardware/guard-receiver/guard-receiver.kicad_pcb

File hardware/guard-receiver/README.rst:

Guard receiver PCB
==================

The R3 field drawing specifies the polarized remote KPS1 coil and its
socket-mounted D9. Check the terminal numbers on the **non-indicating**
P7SA-10F base before applying power.

This 68 × 48 mm, two-layer PCB belongs in the cabinet beside the independent
guard equipment. J36 brings the controller heartbeat and raw panel STOP to two
high-impedance comparator inputs. Separate optocouplers convert them to
24 V signals on J4. A distinct, deenergized-open Omron KFB1 contact returns
the actual HOST guard permission on J31. The hardwired high-high float and
original STOP operate the external guard directly in both HOST and LOCAL.
See the `cabinet schematic <../starter-guard/guard-schematic.pdf>`_ and
`field connection guide <../main-compact-dual/exports/starter-wiring.pdf>`_.

Harnesses
---------

Label both ends by reference and cavity number. Crimp off the board and check
pin 1 at both **mating faces** before power. Both service plugs for J36 and
J31 go straight through between the corresponding board headers.

.. list-table::
   :header-rows: 1
   :widths: 17 35 48

   * - Header
     - Mating part
     - Cavity order and purpose
   * - J36 logic
     - JST ZER-05V-S, SZE-002T-P0.3
     - 1 controller ground, 2 HOST sense, 3 LOCAL sense, 4 heartbeat, 5 raw panel-STOP return. Mate to main J36.
   * - J31 permit
     - Phoenix Contact 1803578, MC 1,5/2-ST-3,81
     - 1 STOP_RETURN and 2 K1-coil permission. Mate to main J31. KFB1 COM4 and NO8 are the only contact between these wires. No shunt.
   * - J2 position
     - JST PHR-3, SPH-002T-P0.5S
     - 1 logic common, 2 isolated HOST full-seat NO, 3 isolated LOCAL full-seat NO. Wire each contact only between its respective pin and pin 1.
   * - J3 receiver supply
     - JST PHR-2, SPH-002T-P0.5S
     - 1 floating +5 V from DDR-15G-5 +Vo, 2 receiver 0 V from -Vo. Set and verify 5.00 V before plugging in.
   * - J4 cabinet
     - JST VHR-5N, SVH-21T-P1.1
     - 1 fused regulated +24 V, 2 cabinet 0 V, 3 PNP heartbeat to WD1, 4 PNP raw panel OK to KPS1 positive coil terminal 0, 5 +24 V HOST feedback drive from the KS1/KS2 auxiliaries and independent HOST contact.

Use 26 AWG with 0.76–1.2 mm jacket OD for the ZE logic loom. PH contacts
accept 24–28 AWG at roughly 0.9–1.5 mm insulation OD. Use 22 AWG, with
1.7–3.0 mm OD insulation, for the specified VH contacts. Use 24 AWG flexible
wire and the correct terminal preparation for the J31 screw plugs.
Cable engineering must satisfy the specific connector and field rating.
Install tie-downs at each enclosure boundary to prevent pulling on the headers.

J2, J3 and J4 have distinct mating housings. J36 and J31 retain the intentional
one-to-one connection to their main-board counterparts. Keep the logic loom
short, inside the cabinet, and away from contactor wiring. Use 300 mm as the
prototype maximum J36 run and verify the actual cable with contactor and radio
switching. Route J4 with its own 0 V return, away from the CT, mains and
capacitor circuits. J31 remains electrically isolated from the cabinet rail.

KPS1 coil terminal **1** returns to cabinet 0 V. Fit D9 (1N4007)
**at that remote coil**, band to positive terminal **0**, in addition to the receiver
clamp D3. KFB1's local clamp D6 is on this PCB. J4.5 energizes KFB1 only
after both motor contactors physically pick up in HOST. Releasing either
contactor, moving to LOCAL, or losing the guard's 24 V opens J31. Never
power drive J4.5 from a lasting 24 V rail. The factory regulator supplies
the logic island through J3. Leave its return isolated from cabinet 0 V
and protective earth. The receiver has no motor or mains terminals.

Supply and driver limits
------------------------

Set the cabinet rail to 24.0 V. Commission it within 22.8–25.2 V at J4.1
with the coils switching and the longest installed cable. The upper bound
leaves margin below D7's 26 V continuous standoff. At 23 °C the selected
four-pole G7SA panel relay has a 1.60 kΩ coil, ±15%. This represents
approximately 12.4–18.5 mA over the stated rail range before cable and
driver drops. Verify voltage directly at the coil and prove pickup and
release at the installed temperature limits.
`Omron G7SA coil data <https://www.ia.omron.com/products/family/386/specification.html>`_
and `Vishay SMBJ data <https://www.vishay.com/docs/88392/smbj.pdf>`_.

At 25 °C, a 4.75 V logic supply and resistor tolerances give at least
4.53 V on the active MOSFET gate before device leakage. Budgeting 1.65 V
for the optocoupler LED and 5.3 Ω for the 2N7002 gives at least 5.42 mA
through the LED. The VO617A-3 specifies 100% minimum current-transfer
ratio at 5 mA and 5 V across its phototransistor. At the high 25.2 V rail
the 10 kΩ output-drive resistor draws at most 2.55 mA even with its
1% tolerance and zero junction drops. These calculations establish a room-
temperature drive budget. Include hot/cold optocoupler gain, off leakage,
the actual WD1 input current and remote-coil flyback in commissioning.
`Nexperia 2N7002 data <https://assets.nexperia.com/documents/data-sheet/2N7002.pdf>`_
and `Vishay VO617A data <https://www.vishay.com/docs/83430/vo617a.pdf>`_.

Mounting and validation
-----------------------

Use four insulating M2.5 standoffs. The four 2.7 mm nonplated mounting holes
are on a 62 × 42 mm pattern with each centre 3 mm from its adjacent edges.
Allow separate clearance for the side-entry cables and the top-entry J2/J3
plugs. Both layers are reserved for the two extra-low-voltage domains.
Keep the clearance corridor clear of metal mounting hardware and cable clips.

The released layout uses 0.25–0.80 mm tracks with 0.85 mm copper / 0.40 mm
drill vias. The independently measured minimum projected separation between
the isolated and 24 V copper is 3.10 mm including the ground pours. Native
KiCad checked all 115 netlisted pads. Nominal geometry checked all 65 drilled
features against SMT solder-mask openings. These are prototype design
measurements before fabrication/registration tolerances.

U1's positive supply pin reaches the 100 nF capacitor on a 3.05 mm
top-layer path. U1 and the capacitor connect to the isolated return plane
through local vias 0.90 mm and 1.27 mm from their respective pad centres.
J4.1 reaches the 24 V TVS on a 4.32 mm long, 0.80 mm wide top trace.
The TVS ground pad reaches its own cabinet-plane via in 1.70 mm.
Both flyback clamps have 1.50 mm returns. These are measured copper lengths.
Surge clamping voltage, ringing and release times require bench measurements.

The `native KiCad project <guard-receiver.kicad_pro>`_, `BOM <bom.csv>`_,
`ERC <checks/erc.json>`_, `routing/parity report <checks/drc.json>`_ and
`geometry audit <checks/geometry.json>`_ accompany the prototype. The `assembly positions <assembly-positions.csv>`_,
`top assembly drawing <assembly-top.svg>`_ and
`pin-by-pin schematic <receiver-schematic.pdf>`_ identify the populated parts.
The reviewed router session is saved beside the PCB.
Confirm actual supply levels, cable dropout, contact wetting and guard release
times at temperature. Test low, high and in-band interference on the open or
frozen heartbeat wire. A legitimate-looking in-band waveform still requires
physical immunity testing. The two independent physical trip switches continue
to interrupt the motor permission even with a falsely asserted HOST-health input.

`JST ZE <https://www.jst.com/wp-content/uploads/2025/06/eZE.pdf>`_,
`PH <https://www.jst-mfg.com/product/pdf/eng/ePH.pdf>`_,
`VH <https://www.jst-mfg.com/product/pdf/eng/eVH.pdf>`_ and
`Phoenix MC mating connector <https://www.phoenixcontact.com/en-gb/products/pcb-plug-mc-15-2-st-381-1803578>`_.

Prototype fabrication
---------------------

Use the `GUARD-RX-A bare-board Gerbers and drills <guard-receiver-rev-a-gerber-prototype.zip>`_
for the receiver. Select a two-layer, 68 × 48 mm board with green solder mask.
The `paste layers for a stencil <guard-receiver-rev-a-stencil-prototype.zip>`_
are a separate upload. The `CAM package checks <checks/cam-package.json>`_
record the source hash, outline, native pin/net and drill comparison, and archive
checksums. Electrical performance requires the populated cabinet tests.

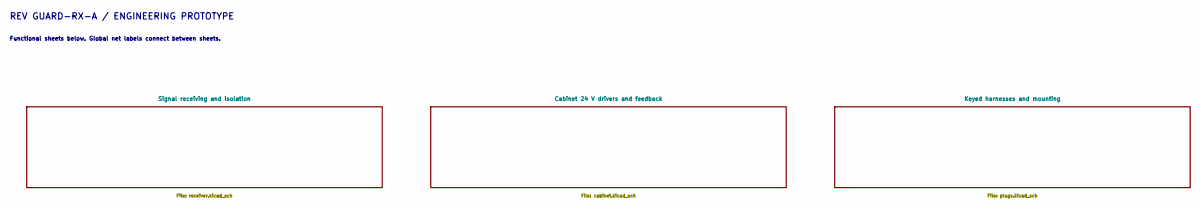
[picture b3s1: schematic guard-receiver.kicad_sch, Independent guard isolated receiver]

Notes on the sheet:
REV GUARD-RX-A / ENGINEERING PROTOTYPE
Functional sheets below. Global net labels connect between sheets.
